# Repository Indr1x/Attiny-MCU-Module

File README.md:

# Attiny-MCU-Module
Atmel Attiny MCU module for devolopment Board Pinboard II

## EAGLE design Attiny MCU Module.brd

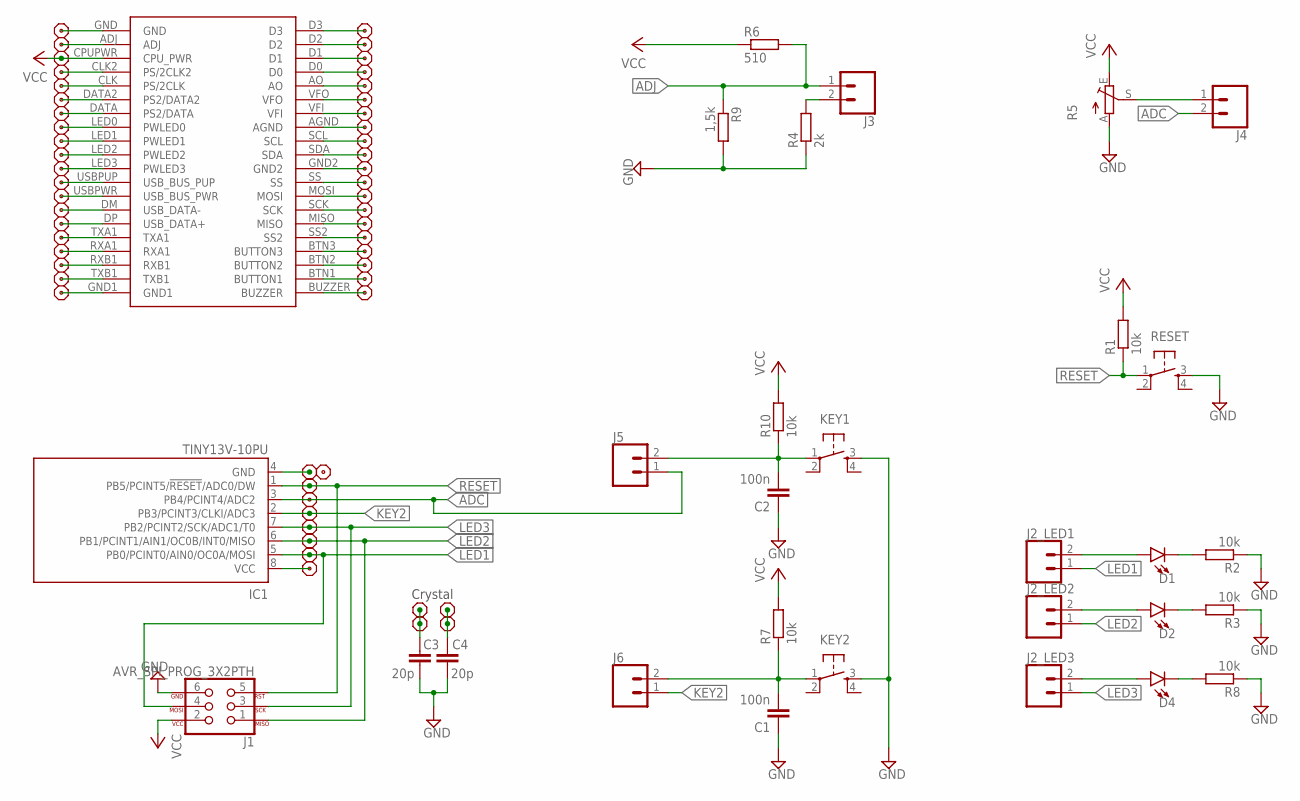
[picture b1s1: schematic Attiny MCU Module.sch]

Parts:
C1, C2: 100n; C1206
C3, C4: 20p; C1206
D1, D2, D4: LED1206; LED-1206
IC1: TINY13V-10PU; DIL08
J1: AVR_SPI_PROG_3X2PTH; 2X3
J2_LED1, J2_LED2, J2_LED3, J3, J4, J5, J6: CONN_02; 1X02
JP1, JP2, JP3, JP4, JP5, JP6, JP7, JP8, JP9, JP10, JP11, JP12, JP13: PINHD-1X1PIN; 1X01
KEY1, KEY2: TAC_SWITCHPTH; TACTILE-PTH
R1, R2, R3, R7, R8, R10: 10k; M1206
R4: 2k; M1206
R5: TRIM_EU-B25P; B25P
R6: 510; M1206
R9: 1,5k; M1206
RESET: TAC_SWITCHPTH; TACTILE-PTH
U$1: CPU_CON; CPU_SHIELD
U$2, U$3: PINHD1X20

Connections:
ADC: IC1.3 (PB4/PCINT4/ADC2), J4.2, J5.1, JP3.1
ADJ: J3.1, R6.2, R9.1, U$1.ADJ, U$3.19
GND: C1.1, C2.1, C3.1, C4.1, IC1.4 (GND), J1.6, JP1.1, KEY1.3, KEY2.3, R2.1, R3.1, R4.1, R5.A, R8.1, R9.2, RESET.3, U$1.GND, U$1.GND1, U$1.GND2, U$2.10, U$3.1, U$3.20
KEY2: IC1.2 (PB3/PCINT3/CLKI/ADC3), J6.1, JP4.1
LED1: IC1.5 (PB0/PCINT0/AIN0/OC0A/MOSI), J1.4, J2_LED1.1, JP7.1
LED2: IC1.6 (PB1/PCINT1/AIN1/OC0B/INT0/MISO), J1.1, J2_LED2.1, JP6.1
LED3: IC1.7 (PB2/PCINT2/SCK/ADC1/T0), J1.3, J2_LED3.1, JP5.1
unnamed: C3.2, JP10.1, JP11.1
unnamed: D1.A, J2_LED1.2
unnamed: D1.C, R2.2
unnamed: D2.C, R3.2
unnamed: D2.A, J2_LED2.2
unnamed: D4.A, J2_LED3.2
unnamed: C4.2, JP9.1, JP12.1
unnamed: D4.C, R8.2
unnamed: U$1.AO, U$2.16
unnamed: J3.2, R4.2
unnamed: U$1.BUZZER, U$2.1
unnamed: U$1.BTN1 (BUTTON1), U$2.2
unnamed: U$1.BTN2 (BUTTON2), U$2.3
unnamed: U$1.BTN3 (BUTTON3), U$2.4
unnamed: U$1.SS2, U$2.5
unnamed: U$1.MISO, U$2.6
unnamed: U$1.SCK, U$2.7
unnamed: U$1.MOSI, U$2.8
unnamed: U$1.SS, U$2.9
unnamed: U$1.SDA, U$2.11
unnamed: U$1.SCL, U$2.12
unnamed: U$1.AGND, U$2.13
unnamed: U$1.VFI, U$2.14
unnamed: U$1.VFO, U$2.15
unnamed: U$1.D0, U$2.17
unnamed: U$1.D1, U$2.18
unnamed: U$1.D2, U$2.19
unnamed: U$1.D3, U$2.20
unnamed: U$1.TXB1, U$3.2
unnamed: U$1.RXB1, U$3.3
unnamed: U$1.RXA1, U$3.4
unnamed: U$1.TXA1, U$3.5
unnamed: U$1.DP (USB_DATA+), U$3.6
unnamed: U$1.DM (USB_DATA-), U$3.7
unnamed: U$1.USBPWR (USB_BUS_PWR), U$3.8
unnamed: U$1.USBPUP (USB_BUS_PUP), U$3.9
unnamed: U$1.LED3 (PWLED3), U$3.10
unnamed: U$1.LED2 (PWLED2), U$3.11
unnamed: U$1.LED1 (PWLED1), U$3.12
unnamed: U$1.LED0 (PWLED0), U$3.13
unnamed: U$1.DATA (PS2/DATA), U$3.14
unnamed: U$1.DATA2 (PS2/DATA2), U$3.15
unnamed: U$1.CLK (PS/2CLK), U$3.16
unnamed: U$1.CLK2 (PS/2CLK2), U$3.17
unnamed: J4.1, R5.S
unnamed: C1.2, J6.2, KEY2.1, R7.1
unnamed: C2.2, J5.2, KEY1.1, R10.1
RESET: IC1.1 (PB5/PCINT5/!RESET!/ADC0/DW), J1.5, JP2.1, R1.1, RESET.1
VCC: IC1.8 (VCC), J1.2, JP8.1, R1.2, R5.E, R6.1, R7.2, R10.2, U$1.CPUPWR (CPU_PWR), U$3.18

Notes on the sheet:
Crystal

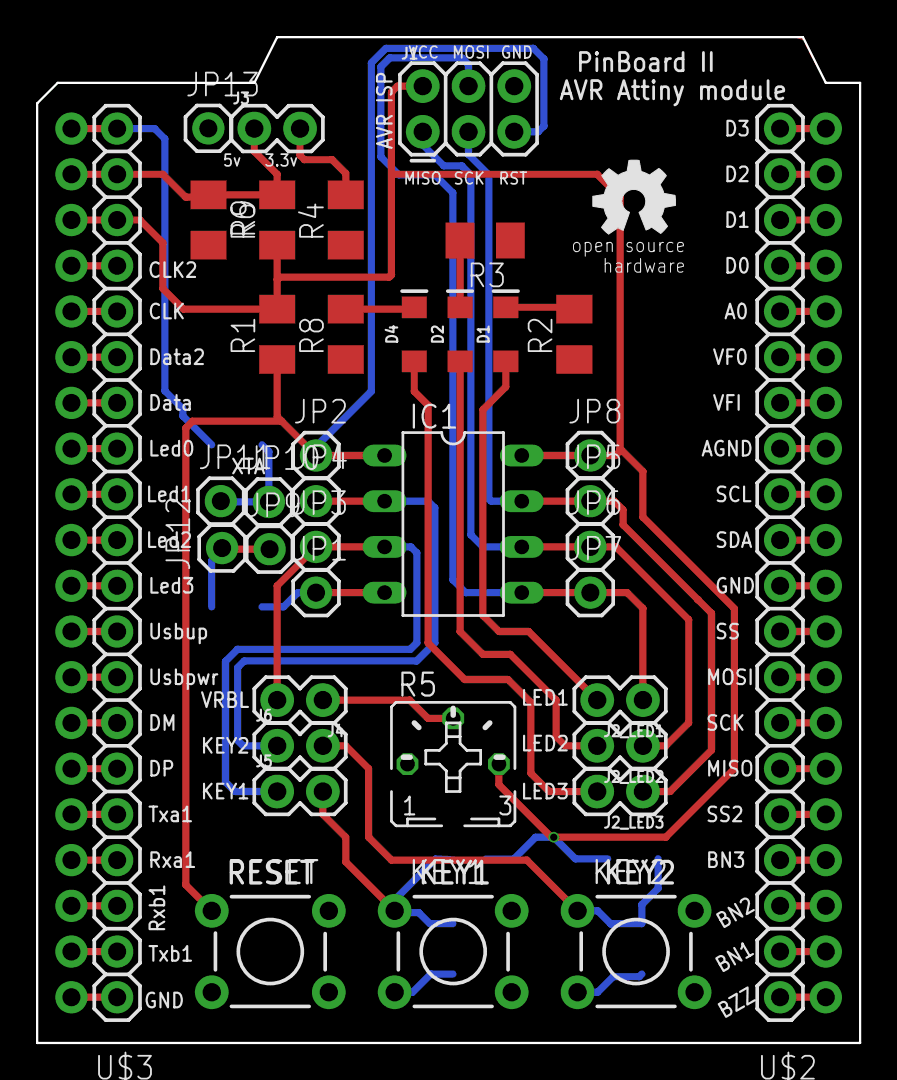
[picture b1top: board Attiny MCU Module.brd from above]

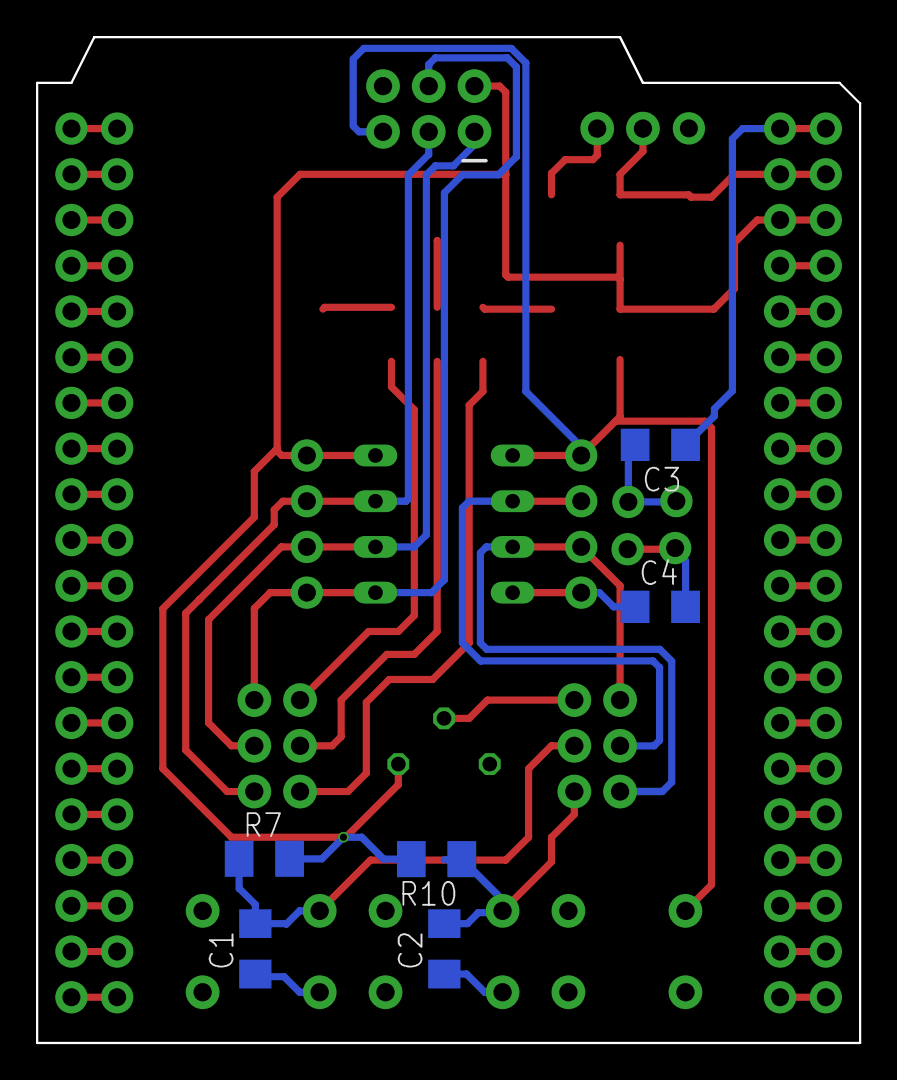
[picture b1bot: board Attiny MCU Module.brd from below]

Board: 2 copper layers, 45.7 x 55.9 mm, 46 parts (6 on the bottom side), 56 nets.

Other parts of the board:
U$4: OSHW_5MM

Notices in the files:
parts and their libraries:
SparkFun-LED: Licensing: Creative Commons ShareAlike 4.0 International - https://creativecommons.org/licenses/by-sa/4.0
